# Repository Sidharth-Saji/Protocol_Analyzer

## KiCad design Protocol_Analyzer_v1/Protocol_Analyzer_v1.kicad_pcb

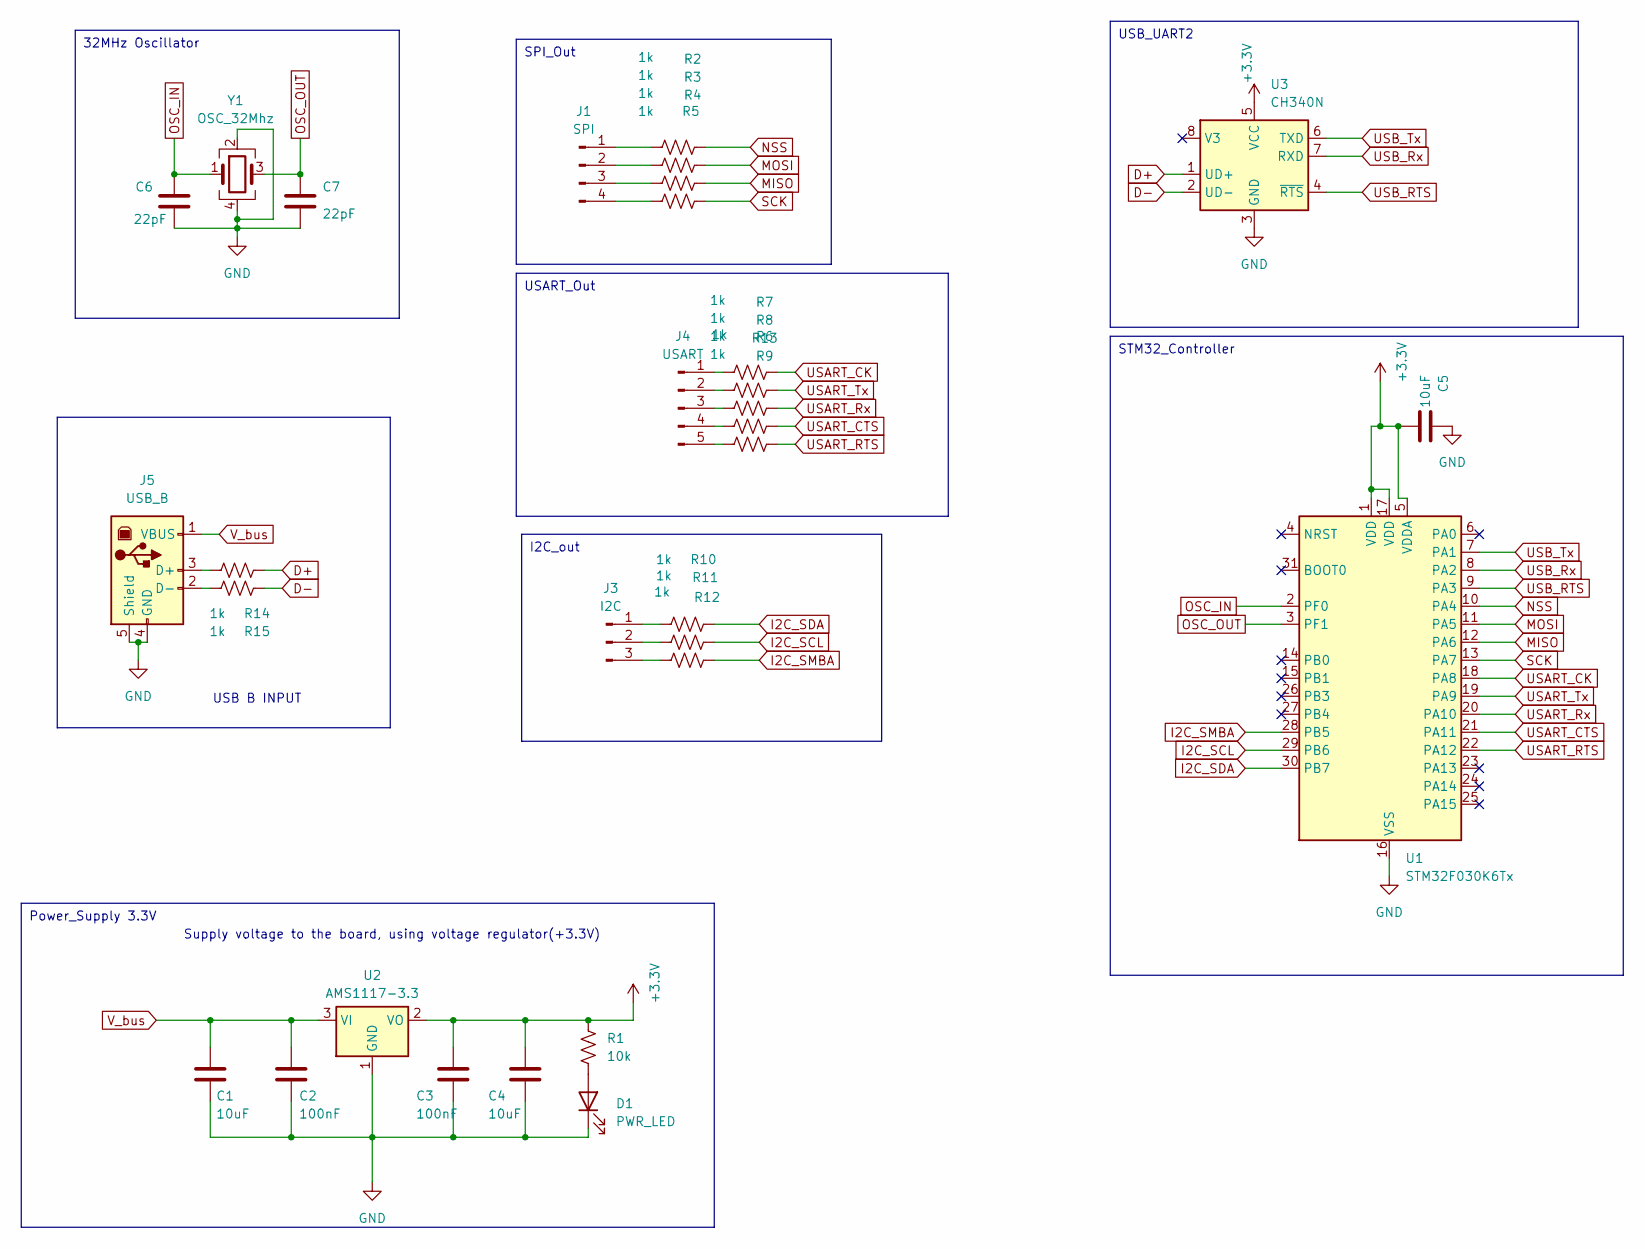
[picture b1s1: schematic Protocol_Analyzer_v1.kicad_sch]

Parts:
C1, C4, C5: 10uF; C_0805_2012Metric
C2, C3: 100nF; C_0805_2012Metric
C6, C7: 22pF; C_0805_2012Metric
D1: PWR_LED; LED_0805_2012Metric
J1: SPI; PinHeader_1x04_P2.54mm_Vertical
J3: I2C; PinHeader_1x03_P2.54mm_Vertical
J4: USART; PinHeader_1x05_P2.54mm_Vertical
J5: USB_B; USB_B_Lumberg_2411_02_Horizontal
R1: 10k; R_0805_2012Metric
R2, R3, R4, R5, R6, R7, R8, R9, R10, R11, R12, R13, R14, R15: 1k; R_0805_2012Metric
U1: STM32F030K6Tx; LQFP-32_7x7mm_P0.8mm
U2: AMS1117-3.3; SOT-223-3_TabPin2
U3: CH340N; SOP-8_3.9x4.9mm_P1.27mm
Y1: OSC_32Mhz; Crystal_SMD_7050-4Pin_7.0x5.0mm

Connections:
+3.3V: C3.1, C4.1, C5.2, R1.2, U1.1 (VDD), U1.5 (VDDA), U1.17 (VDD), U2.2 (VO), U3.5 (VCC)
D+: R14.2, U3.1 (UD+)
D-: R15.2, U3.2 (UD-)
GND: C1.2, C2.2, C3.2, C4.2, C5.1, C6.2, C7.2, D1.1 (K), J5.4 (GND), J5.5 (Shield), U1.16 (VSS), U1.32 (VSS), U2.1 (GND), U3.3 (GND), Y1.2, Y1.4
I2C_SCL: R11.2, U1.29 (PB6)
I2C_SDA: R10.2, U1.30 (PB7)
I2C_SMBA: R12.2, U1.28 (PB5)
MISO: R4.2, U1.12 (PA6)
MOSI: R3.2, U1.11 (PA5)
NSS: R2.2, U1.10 (PA4)
unnamed: D1.2 (A), R1.1
unnamed: J1.1, R2.1
unnamed: J1.2, R3.1
unnamed: J1.3, R4.1
unnamed: J1.4, R5.1
unnamed: J3.1, R10.1
unnamed: J3.2, R11.1
unnamed: J3.3, R12.1
unnamed: J4.1, R6.1
unnamed: J4.2, R7.1
unnamed: J4.3, R8.1
unnamed: J4.4, R13.1
unnamed: J4.5, R9.1
unnamed: J5.3 (D+), R14.1
unnamed: J5.2 (D-), R15.1
OSC_IN: C6.1, U1.2 (PF0), Y1.1
OSC_OUT: C7.1, U1.3 (PF1), Y1.3
SCK: R5.2, U1.13 (PA7)
USART_CK: R6.2, U1.18 (PA8)
USART_CTS: R13.2, U1.21 (PA11)
USART_RTS: R9.2, U1.22 (PA12)
USART_Rx: R8.2, U1.20 (PA10)
USART_Tx: R7.2, U1.19 (PA9)
USB_RTS: U1.9 (PA3), U3.4 (~RTS)
USB_Rx: U1.8 (PA2), U3.7 (RXD)
USB_Tx: U1.7 (PA1), U3.6 (TXD)
V_bus: C1.1, C2.1, J5.1 (VBUS), U2.3 (VI)

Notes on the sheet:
USB_UART2
Power_Supply 3.3V
USART_Out
STM32_Controller
SPI_Out
32MHz Oscillator
I2C_out
USB B INPUT
Supply voltage to the board, using voltage regulator(+3.3V)

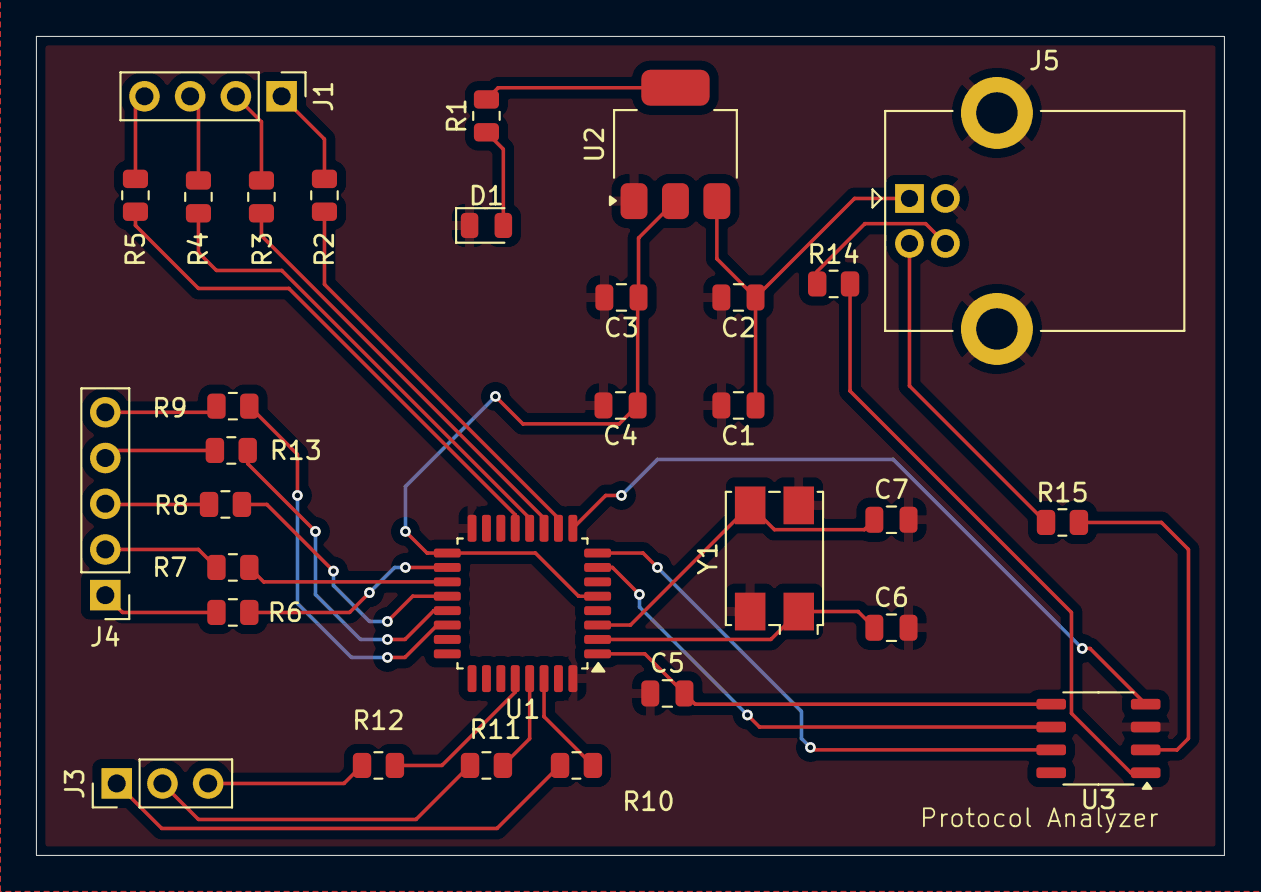
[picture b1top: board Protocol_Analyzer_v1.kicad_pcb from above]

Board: 2 copper layers, 66.0 x 45.5 mm, 31 parts (0 on the bottom side), 37 nets.

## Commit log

2024-10-24 Adding PCB design and initial review of other products
